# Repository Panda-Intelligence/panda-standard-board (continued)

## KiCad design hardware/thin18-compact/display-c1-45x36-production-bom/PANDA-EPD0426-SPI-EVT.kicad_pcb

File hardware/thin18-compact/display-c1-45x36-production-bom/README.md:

# Display-C1 display board

45 × 36 mm, two copper layers. Native DRC/open/parity/ERC: 0/0/0/0.
U1-U3 use AIP74LVC2G17GC363.TR, Wuxi I-core, LCSC C3294722.
J1 remains DF40C-60DP-0.4V(51), bottom side at (23,4) mm, rotation 0°.
The exact connector, panel FPC, MOSFET and inductor contracts remain retained.
Active production data is ../production/display-c1-45x36/.
manufacturing_release=false; physical EVT and actual fit remain open.

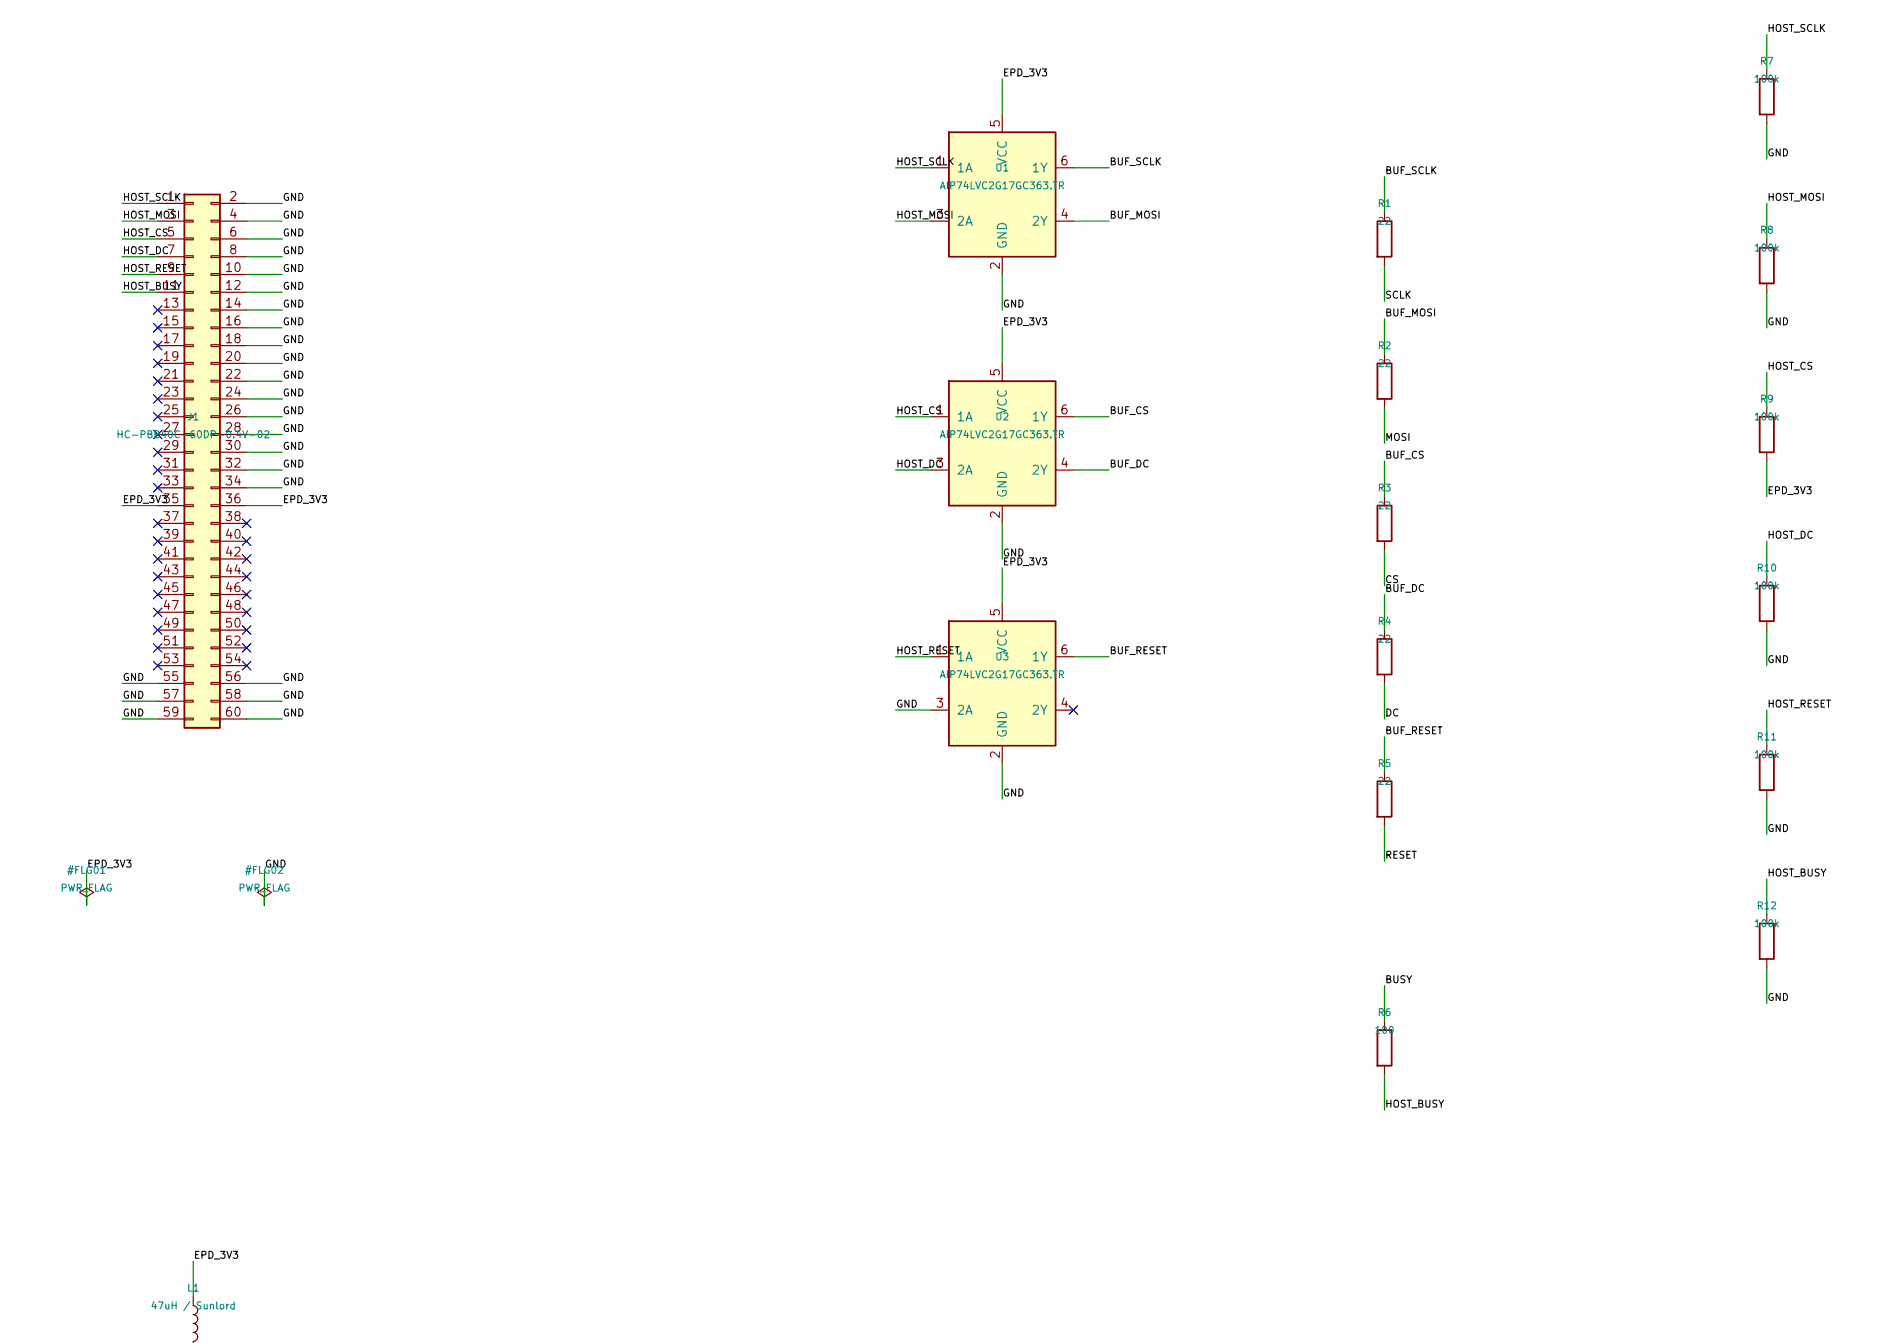
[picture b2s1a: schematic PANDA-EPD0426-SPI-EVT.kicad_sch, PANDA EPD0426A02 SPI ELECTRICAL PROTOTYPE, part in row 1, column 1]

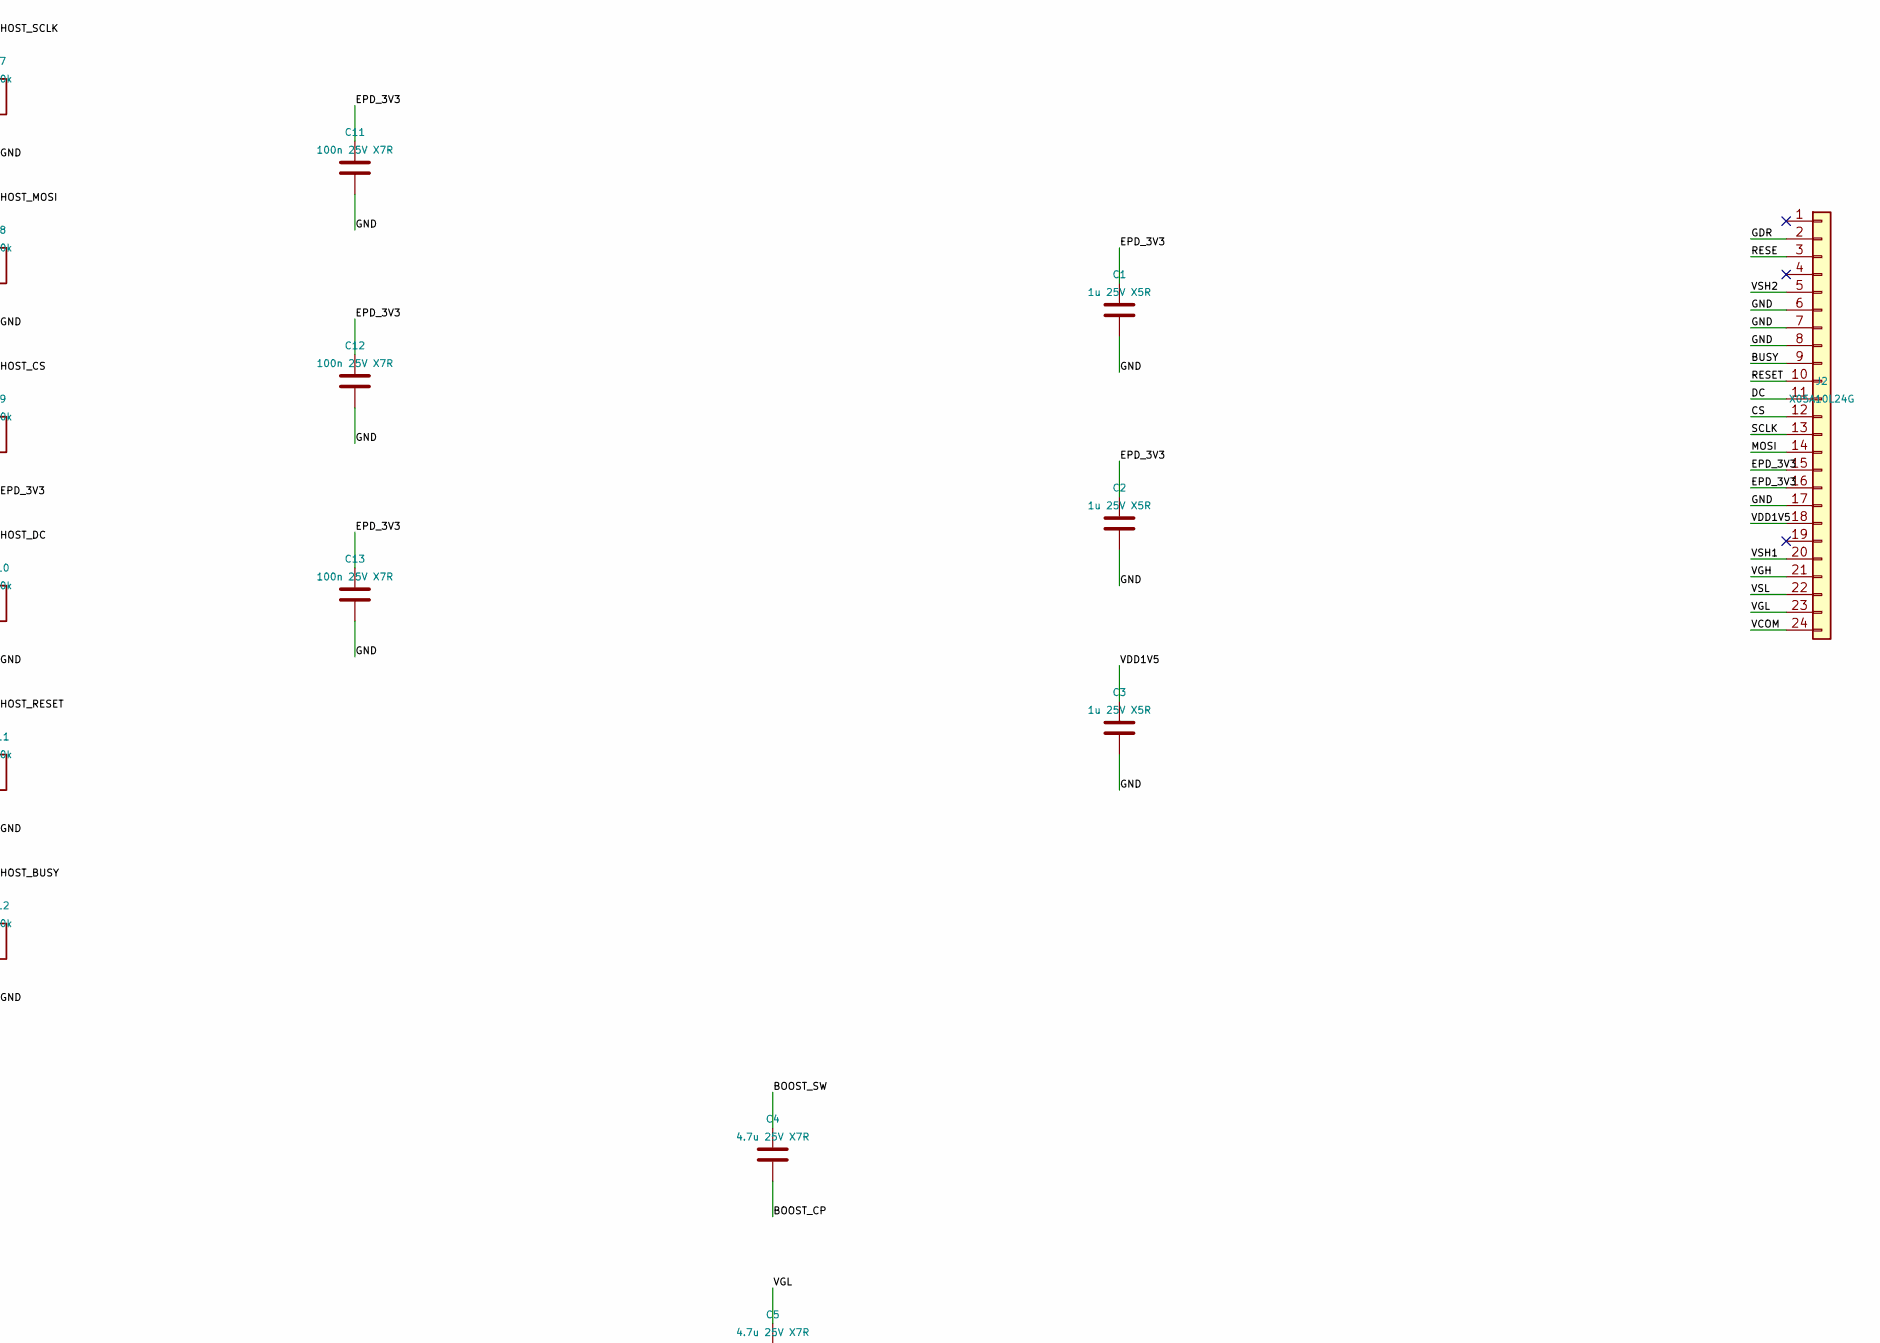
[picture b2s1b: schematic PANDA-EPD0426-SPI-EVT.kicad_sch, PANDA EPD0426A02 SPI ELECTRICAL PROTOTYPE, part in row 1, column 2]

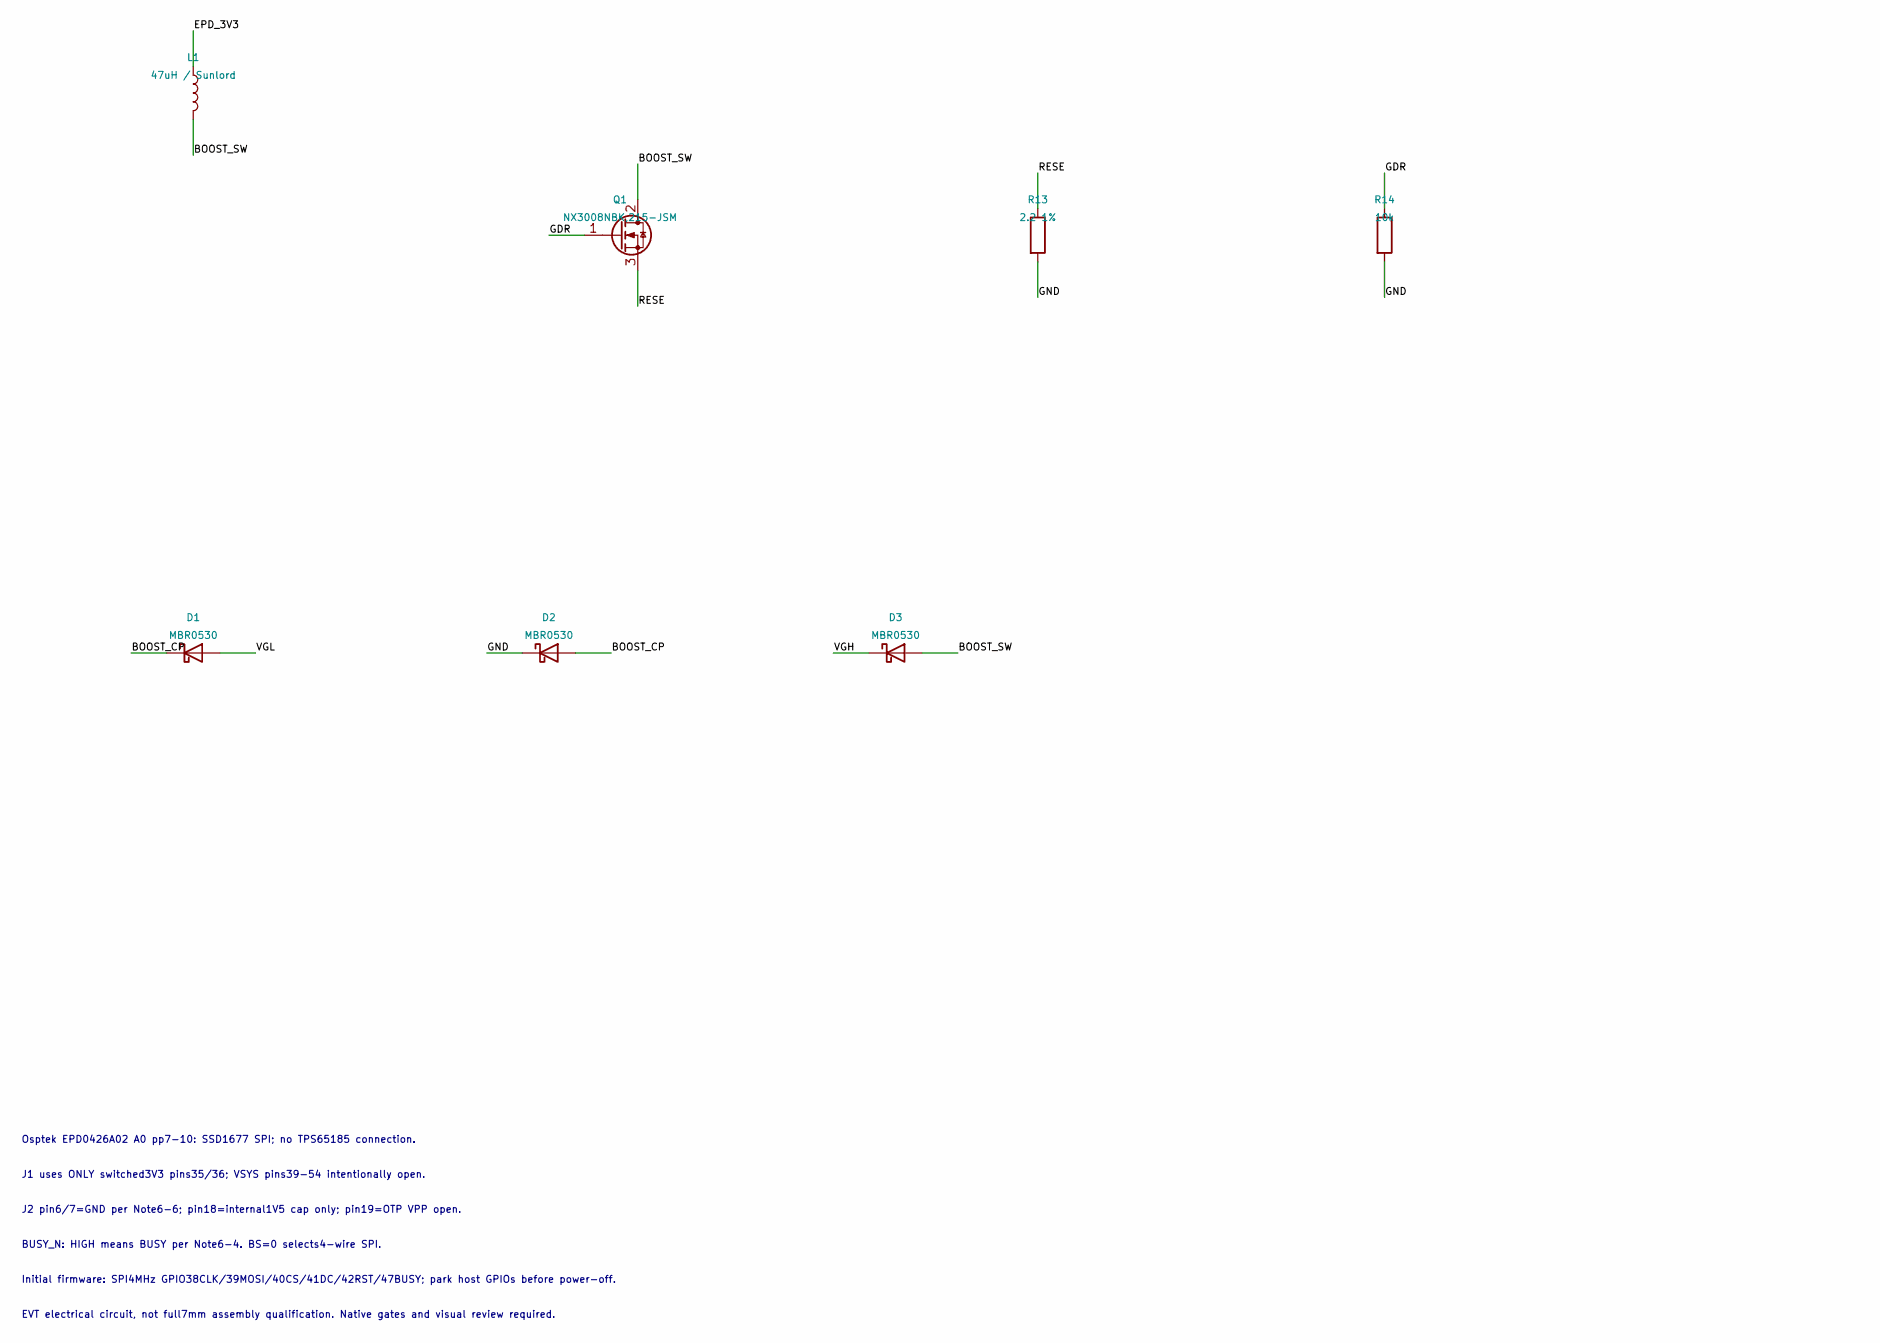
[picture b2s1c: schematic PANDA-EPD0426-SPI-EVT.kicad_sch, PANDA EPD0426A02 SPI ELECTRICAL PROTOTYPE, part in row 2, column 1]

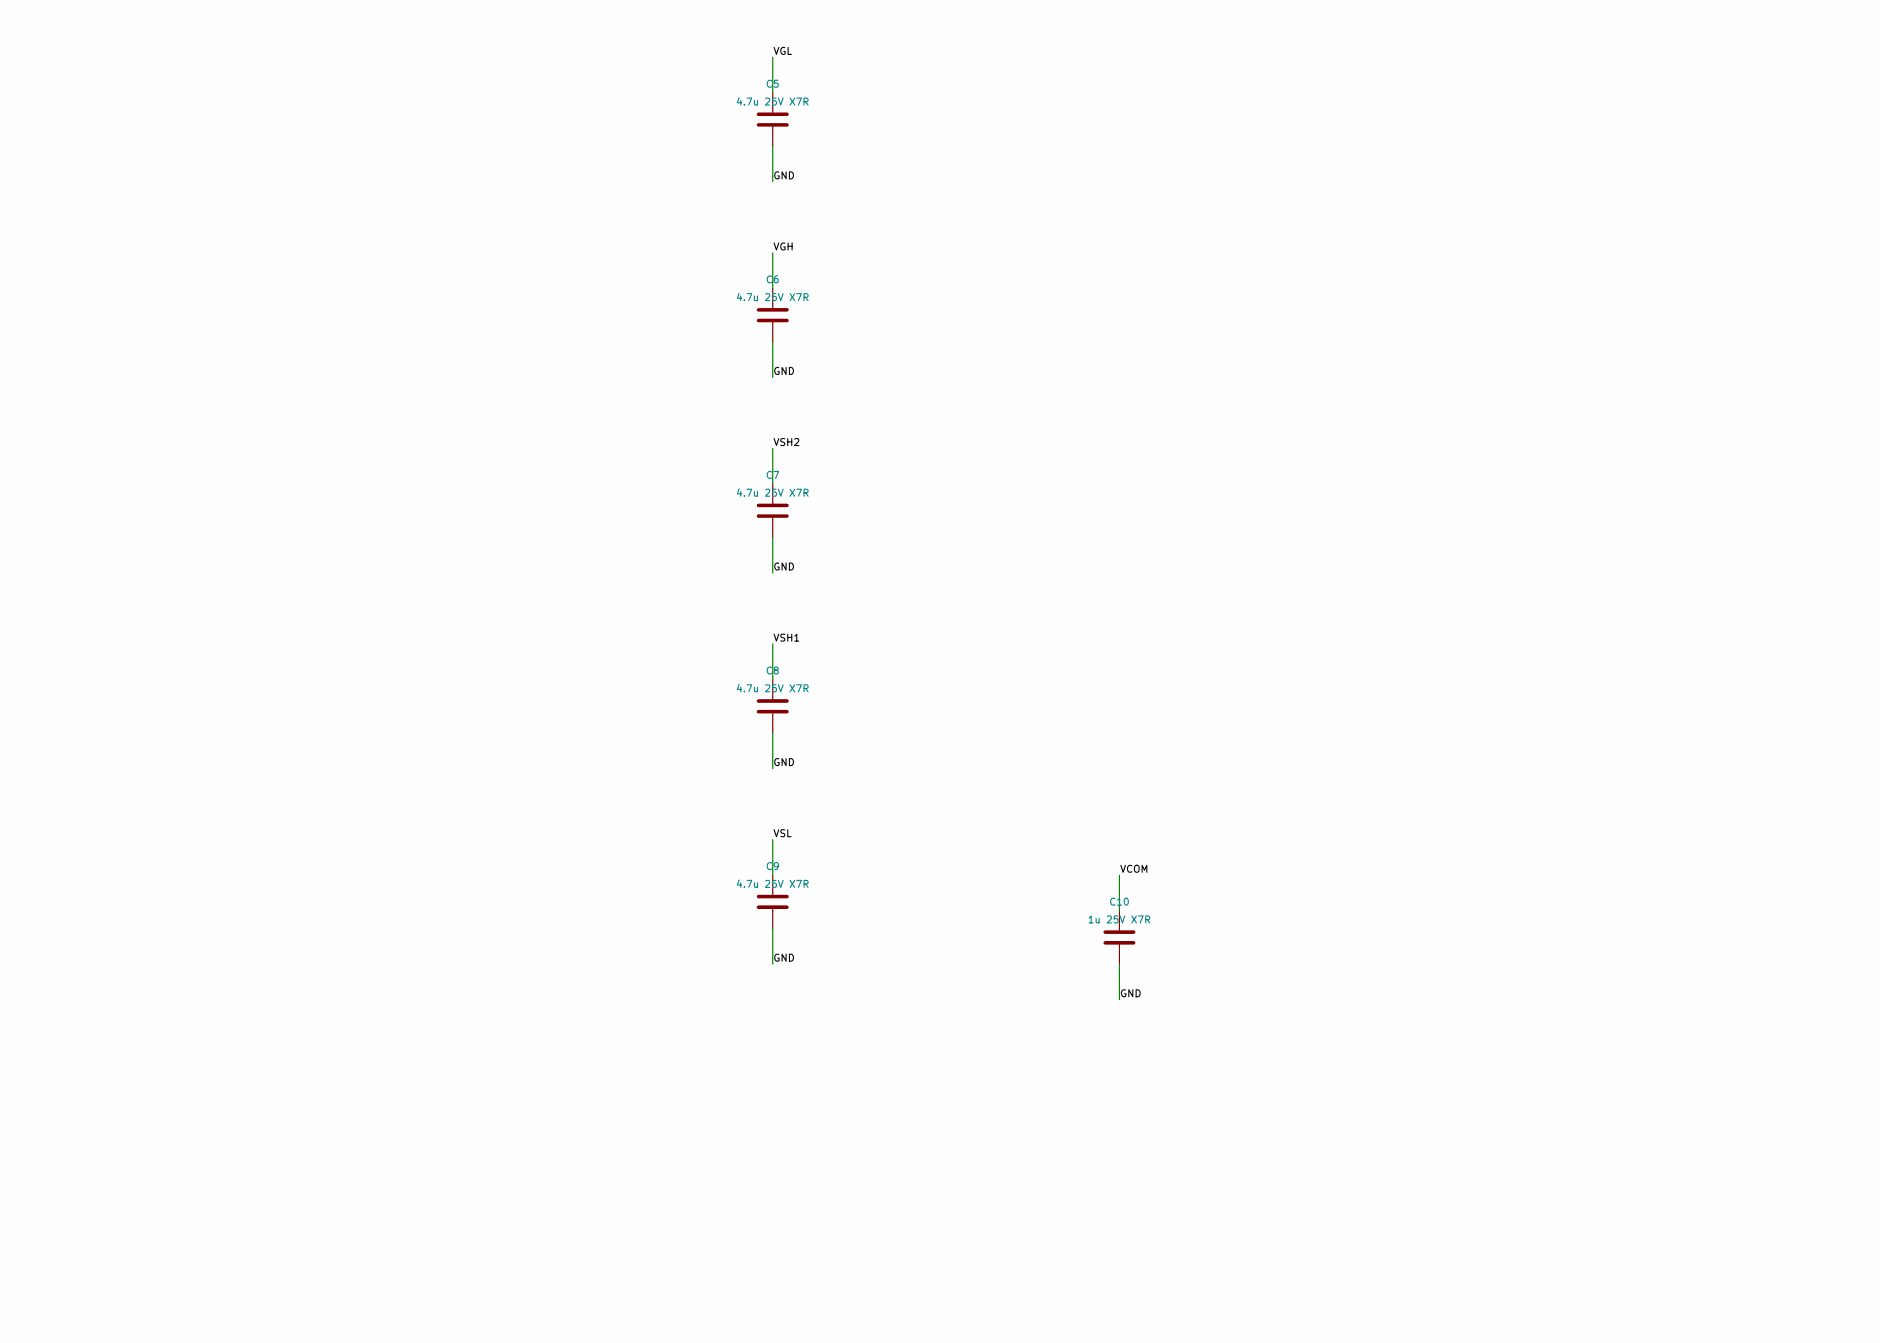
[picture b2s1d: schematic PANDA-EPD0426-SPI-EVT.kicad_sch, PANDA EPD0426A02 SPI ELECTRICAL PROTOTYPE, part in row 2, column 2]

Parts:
C1, C2, C3: 1u 25V X5R; C_0603_1608Metric; MPN 0603B105K250NT; LCSC C59302
C4, C5, C6, C7, C8, C9: 4.7u 25V X7R; C_0805_2012Metric; MPN 0805B475K250NT; LCSC C37818
C10: 1u 25V X7R; C_0805_2012Metric; MPN 0805B105K250NT; LCSC C89190
C11, C12, C13: 100n 25V X7R; C_0603_1608Metric; MPN 0603B104K250NT; LCSC C694249
D1, D2, D3: MBR0530; MBR0530_JSCJ_SOD123; MPN MBR0530; LCSC C77336
J1: HC-PBB40C-60DP-0.4V-02; HCTL_PBB40C_60DP_04V; MPN HC-PBB40C-60DP-0.4V-02; LCSC C19089235
J2: X05A10L24G; XKB_X05A10L24G; MPN X05A10L24G; LCSC C2880917
L1: 47uH / Sunlord; Sunlord_SWPA3012_47u; MPN SWPA3012S470MT; LCSC C83420
Q1: NX3008NBK,215-JSM; JSM_NX3008NBK_SOT23; MPN NX3008NBK,215-JSM; LCSC C53113911
R1, R2, R3, R4, R5: 22; R_0402_1005Metric; MPN RC-02K22R0FT; LCSC C324769
R6: 100; R_0402_1005Metric; MPN RC-02K1000FT; LCSC C140217
R7, R8, R9, R10, R11, R12: 100k; R_0402_1005Metric; MPN RC-02K1003FT; LCSC C140219
R13: 2.2 1%; R_0603_1608Metric; MPN RS-03L2R20FT; LCSC C322118
R14: 10k; R_0402_1005Metric; MPN RC-02K1002FT; LCSC C140215
U1, U2, U3: AIP74LVC2G17GC363.TR; SOT-363_SC-70-6; MPN AIP74LVC2G17GC363.TR; LCSC C3294722

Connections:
/BOOST_CP: C4.2, D1.1 (K), D2.2 (A)
/BOOST_SW: C4.1, D3.2 (A), L1.2, Q1.2 (D)
/BUF_CS: R3.1, U2.6 (1Y)
/BUF_DC: R4.1, U2.4 (2Y)
/BUF_MOSI: R2.1, U1.4 (2Y)
/BUF_RESET: R5.1, U3.6 (1Y)
/BUF_SCLK: R1.1, U1.6 (1Y)
/BUSY: J2.9, R6.1
/CS: J2.12, R3.2
/DC: J2.11, R4.2
/EPD_3V3: C1.1, C2.1, C11.1, C12.1, C13.1, J1.35, J1.36, J2.15, J2.16, L1.1, R9.2, U1.5 (VCC), U2.5 (VCC), U3.5 (VCC)
/GDR: J2.2, Q1.1 (G), R14.1
/GND: C1.2, C2.2, C3.2, C5.2, C6.2, C7.2, C8.2, C9.2, C10.2, C11.2, C12.2, C13.2, D2.1 (K), J1.2, J1.4, J1.6, J1.8, J1.10, J1.12, J1.14, J1.16, J1.18, J1.20, J1.22, J1.24, J1.26, J1.28, J1.30, J1.32, J1.34, J1.55, J1.56, J1.57, J1.58, J1.59, J1.60, J2.6, J2.7, J2.8, J2.17, R7.2, R8.2, R10.2, R11.2, R12.2, R13.2, R14.2, U1.2 (GND), U2.2 (GND), U3.2 (GND), U3.3 (2A)
/HOST_BUSY: J1.11, R6.2, R12.1
/HOST_CS: J1.5, R9.1, U2.1 (1A)
/HOST_DC: J1.7, R10.1, U2.3 (2A)
/HOST_MOSI: J1.3, R8.1, U1.3 (2A)
/HOST_RESET: J1.9, R11.1, U3.1 (1A)
/HOST_SCLK: J1.1, R7.1, U1.1 (1A)
/MOSI: J2.14, R2.2
/RESE: J2.3, Q1.3 (S), R13.1
/RESET: J2.10, R5.2
/SCLK: J2.13, R1.2
/VCOM: C10.1, J2.24
/VDD1V5: C3.1, J2.18
/VGH: C6.1, D3.1 (K), J2.21
/VGL: C5.1, D1.2 (A), J2.23
/VSH1: C8.1, J2.20
/VSH2: C7.1, J2.5
/VSL: C9.1, J2.22

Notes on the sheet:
Osptek EPD0426A02 A0 pp7-10: SSD1677 SPI; no TPS65185 connection.
J1 uses ONLY switched3V3 pins35/36; VSYS pins39-54 intentionally open.
J2 pin6/7=GND per Note6-6; pin18=internal1V5 cap only; pin19=OTP VPP open.
BUSY_N: HIGH means BUSY per Note6-4. BS=0 selects4-wire SPI.
Initial firmware: SPI4MHz GPIO38CLK/39MOSI/40CS/41DC/42RST/47BUSY; park host GPIOs before power-off.
EVT electrical circuit, not full7mm assembly qualification. Native gates and visual review required.

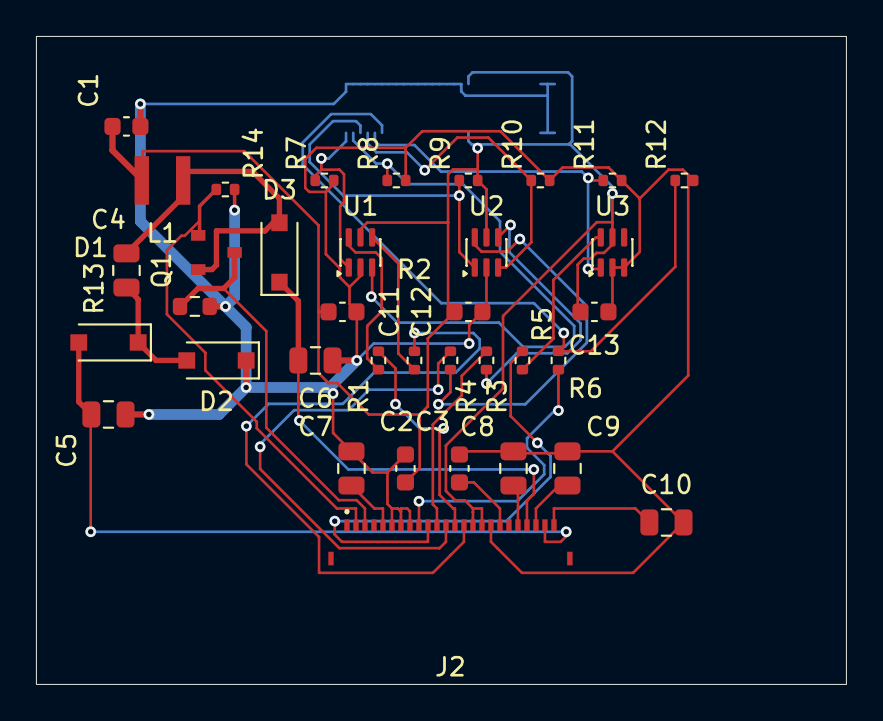
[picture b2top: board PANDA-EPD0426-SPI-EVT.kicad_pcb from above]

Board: 2 copper layers, 45.0 x 36.0 mm, 37 parts (1 on the bottom side), 30 nets.
